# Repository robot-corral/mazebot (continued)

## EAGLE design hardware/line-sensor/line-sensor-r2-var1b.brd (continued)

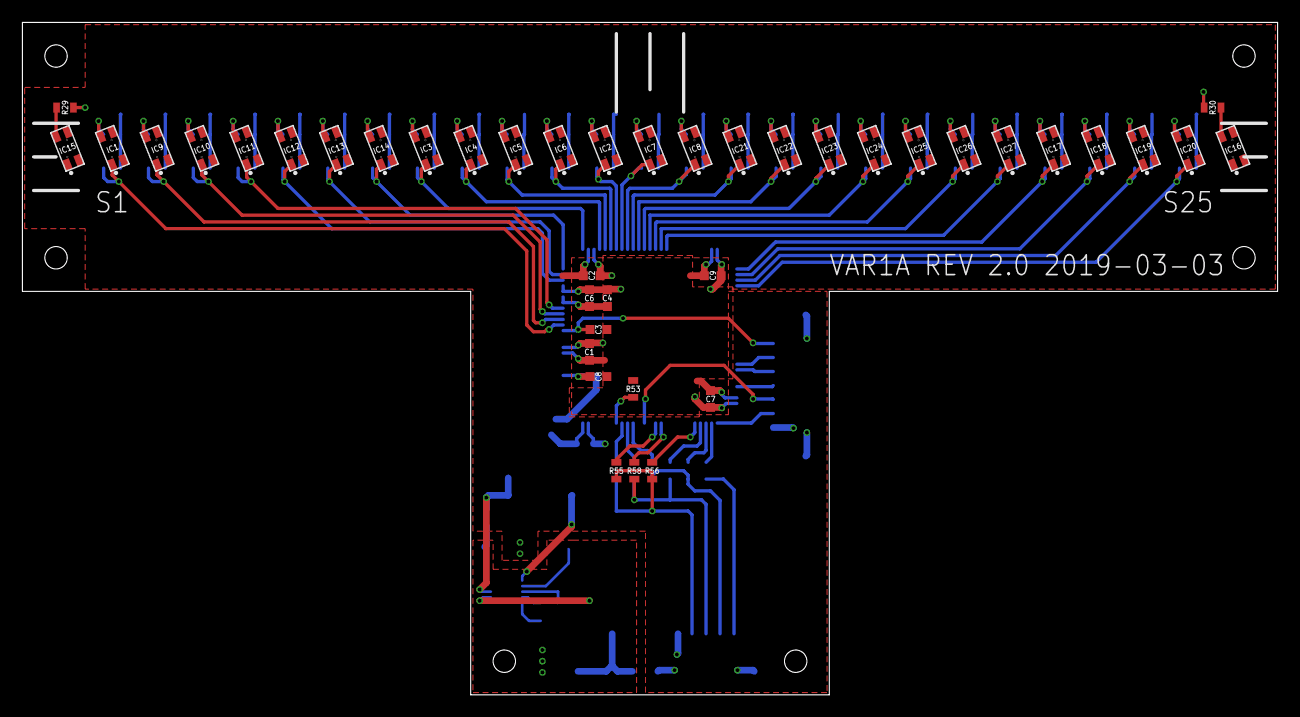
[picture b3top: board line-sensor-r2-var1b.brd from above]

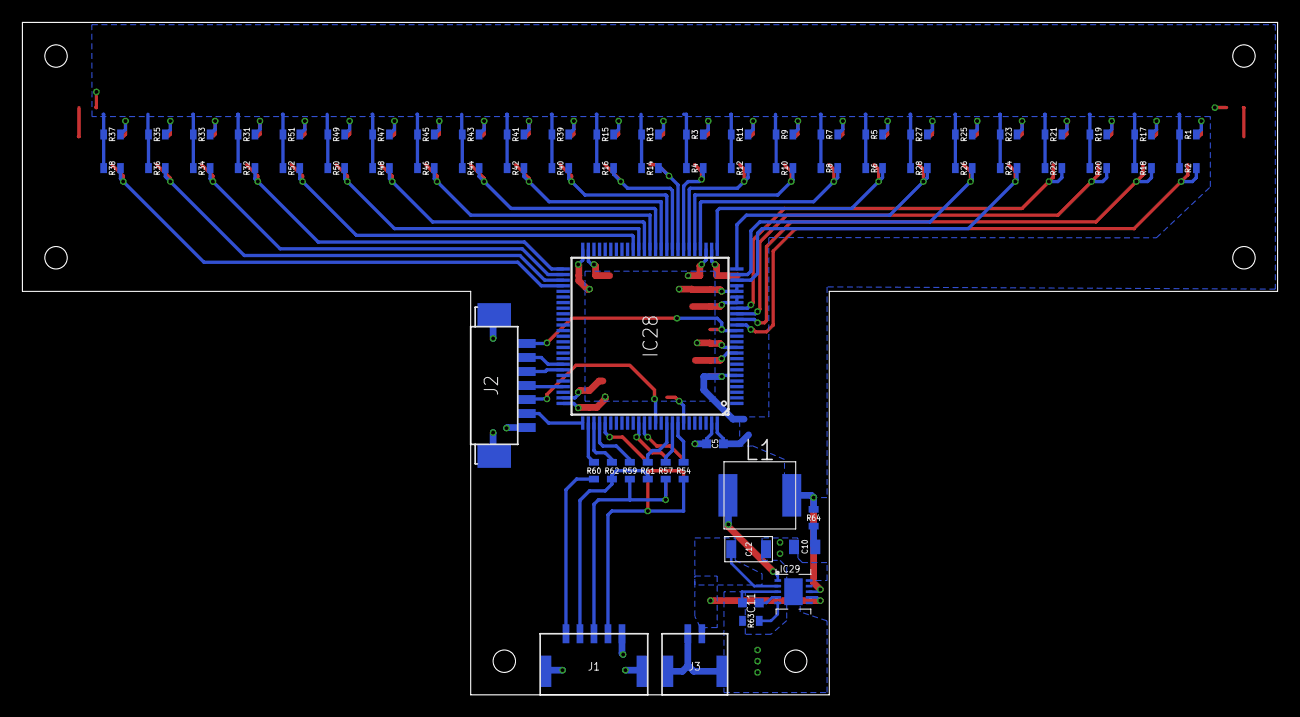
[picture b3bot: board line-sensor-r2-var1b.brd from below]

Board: 2 copper layers, 112.0 x 60.0 mm, 109 parts (68 on the bottom side), 79 nets.

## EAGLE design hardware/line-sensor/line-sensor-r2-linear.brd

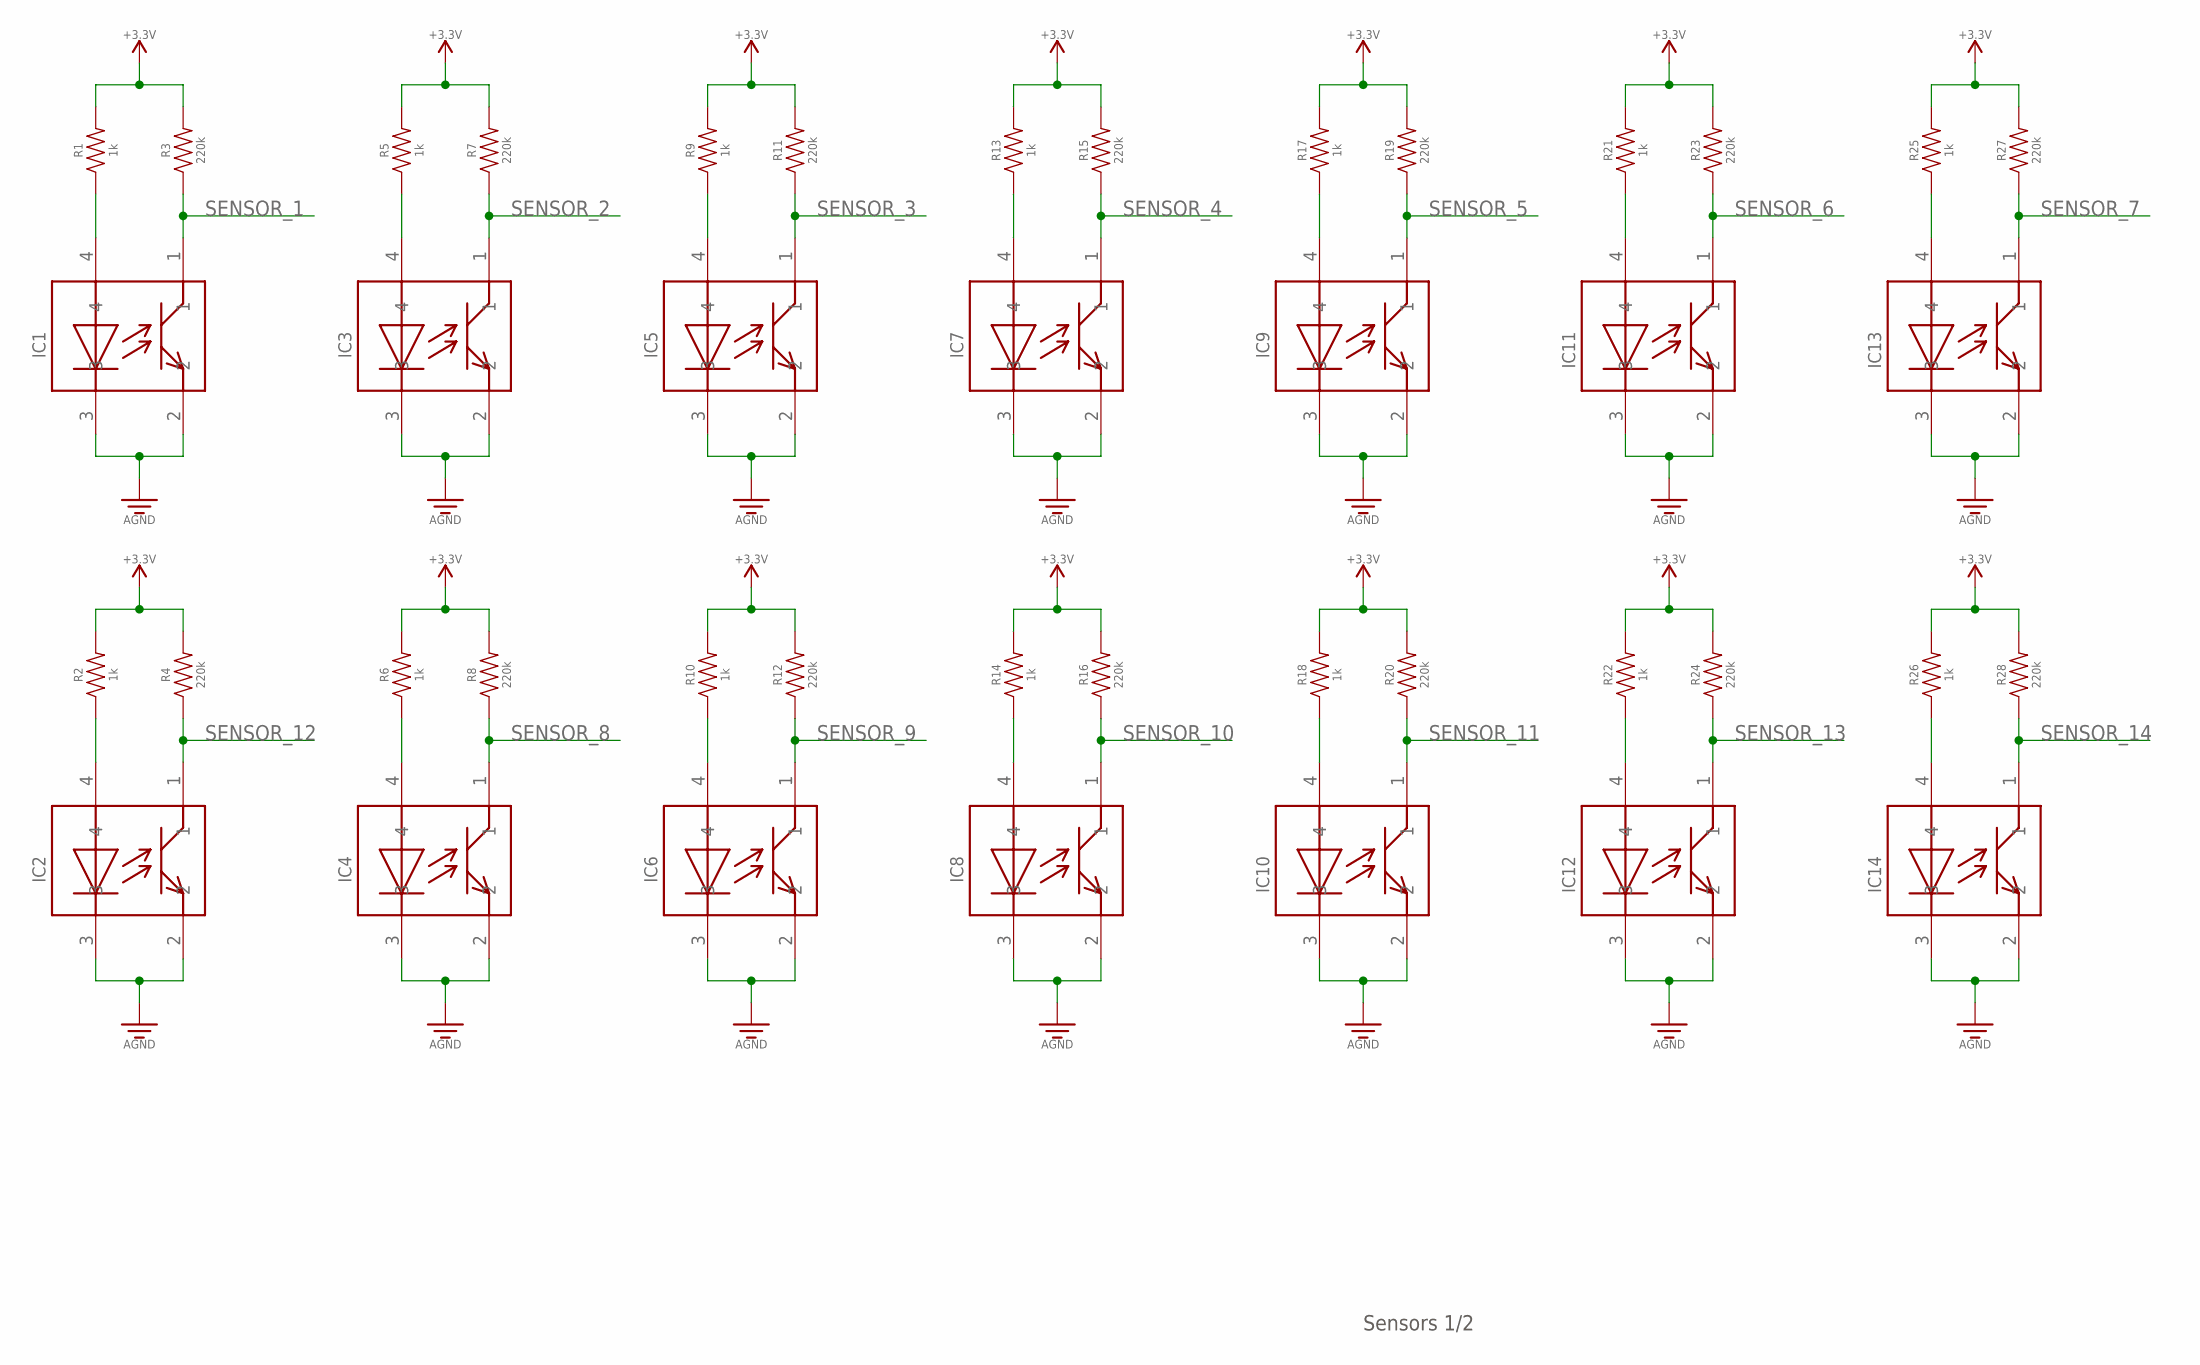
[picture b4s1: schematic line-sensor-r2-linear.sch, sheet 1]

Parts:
IC1, IC2, IC3, IC4, IC5, IC6, IC7, IC8, IC9, IC10, IC11, IC12, IC13, IC14: GP2S60
R1, R2, R5, R6, R9, R10, R13, R14, R17, R18, R21, R22, R25, R26: 1k; RESISTOR-0603
R3, R4, R7, R8, R11, R12, R15, R16, R19, R20, R23, R24, R27, R28: 220k; RESISTOR-0603

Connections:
GND: IC1.2, IC1.3, IC2.2, IC2.3, IC3.2, IC3.3, IC4.2, IC4.3, IC5.2, IC5.3, IC6.2, IC6.3, IC7.2, IC7.3, IC8.2, IC8.3, IC9.2, IC9.3, IC10.2, IC10.3, IC11.2, IC11.3, IC12.2, IC12.3, IC13.2, IC13.3, IC14.2, IC14.3; also elsewhere on the board
unnamed: IC3.4, R5.P$1 (1)
unnamed: IC1.4, R1.P$1 (1)
unnamed: IC5.4, R9.P$1 (1)
unnamed: IC7.4, R13.P$1 (1)
unnamed: IC9.4, R17.P$1 (1)
unnamed: IC11.4, R21.P$1 (1)
unnamed: IC13.4, R25.P$1 (1)
unnamed: IC4.4, R6.P$1 (1)
unnamed: IC6.4, R10.P$1 (1)
unnamed: IC8.4, R14.P$1 (1)
unnamed: IC10.4, R18.P$1 (1)
unnamed: IC2.4, R2.P$1 (1)
unnamed: IC12.4, R22.P$1 (1)
unnamed: IC14.4, R26.P$1 (1)
SENSOR_1: IC1.1, R3.P$1 (1); also elsewhere on the board
SENSOR_2: IC3.1, R7.P$1 (1); also elsewhere on the board
SENSOR_3: IC5.1, R11.P$1 (1); also elsewhere on the board
SENSOR_4: IC7.1, R15.P$1 (1); also elsewhere on the board
SENSOR_5: IC9.1, R19.P$1 (1); also elsewhere on the board
SENSOR_6: IC11.1, R23.P$1 (1); also elsewhere on the board
SENSOR_7: IC13.1, R27.P$1 (1); also elsewhere on the board
SENSOR_8: IC4.1, R8.P$1 (1); also elsewhere on the board
SENSOR_9: IC6.1, R12.P$1 (1); also elsewhere on the board
SENSOR_10: IC8.1, R16.P$1 (1); also elsewhere on the board
SENSOR_11: IC10.1, R20.P$1 (1); also elsewhere on the board
SENSOR_12: IC2.1, R4.P$1 (1); also elsewhere on the board
SENSOR_13: IC12.1, R24.P$1 (1); also elsewhere on the board
SENSOR_14: IC14.1, R28.P$1 (1); also elsewhere on the board
VDDA: R1.P$2 (2), R2.P$2 (2), R3.P$2 (2), R4.P$2 (2), R5.P$2 (2), R6.P$2 (2), R7.P$2 (2), R8.P$2 (2), R9.P$2 (2), R10.P$2 (2), R11.P$2 (2), R12.P$2 (2), R13.P$2 (2), R14.P$2 (2), R15.P$2 (2), R16.P$2 (2), R17.P$2 (2), R18.P$2 (2), R19.P$2 (2), R20.P$2 (2), R21.P$2 (2), R22.P$2 (2), R23.P$2 (2), R24.P$2 (2), R25.P$2 (2), R26.P$2 (2), R27.P$2 (2), R28.P$2 (2); also elsewhere on the board

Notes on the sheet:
Sensors 1/2

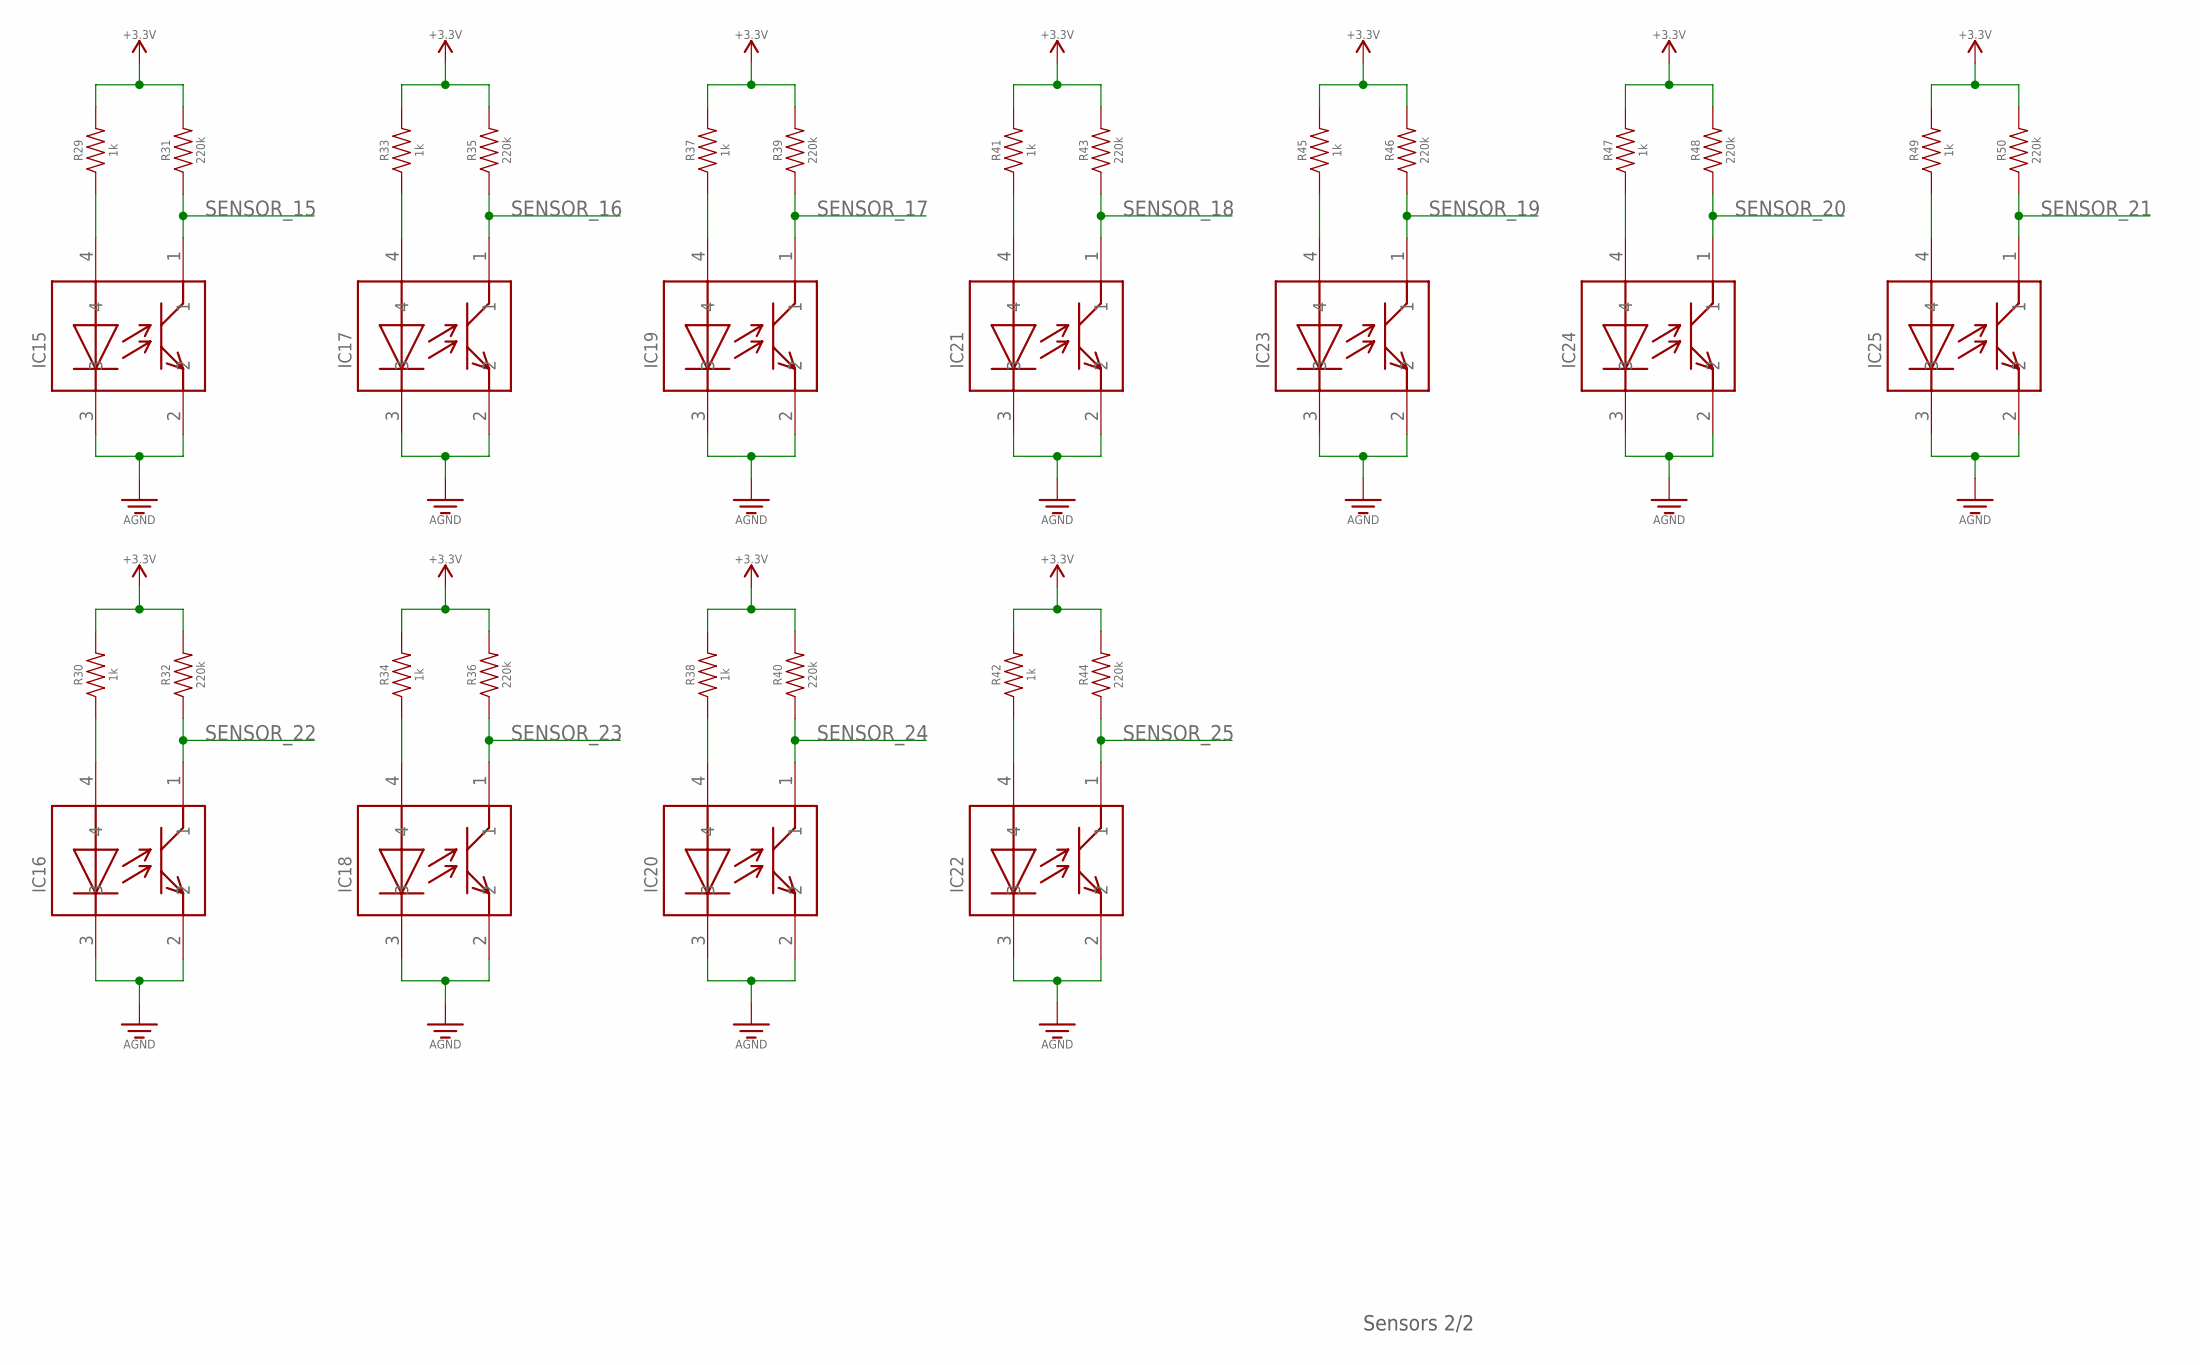
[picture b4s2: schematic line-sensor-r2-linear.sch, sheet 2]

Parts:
IC15, IC16, IC17, IC18, IC19, IC20, IC21, IC22, IC23, IC24, IC25: GP2S60
R29, R30, R33, R34, R37, R38, R41, R42, R45, R47, R49: 1k; RESISTOR-0603
R31, R32, R35, R36, R39, R40, R43, R44, R46, R48, R50: 220k; RESISTOR-0603

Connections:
GND: IC15.2, IC15.3, IC16.2, IC16.3, IC17.2, IC17.3, IC18.2, IC18.3, IC19.2, IC19.3, IC20.2, IC20.3, IC21.2, IC21.3, IC22.2, IC22.3, IC23.2, IC23.3, IC24.2, IC24.3, IC25.2, IC25.3; also elsewhere on the board
unnamed: IC15.4, R29.P$1 (1)
unnamed: IC17.4, R33.P$1 (1)
unnamed: IC19.4, R37.P$1 (1)
unnamed: IC21.4, R41.P$1 (1)
unnamed: IC23.4, R45.P$1 (1)
unnamed: IC24.4, R47.P$1 (1)
unnamed: IC25.4, R49.P$1 (1)
unnamed: IC16.4, R30.P$1 (1)
unnamed: IC18.4, R34.P$1 (1)
unnamed: IC20.4, R38.P$1 (1)
unnamed: IC22.4, R42.P$1 (1)
SENSOR_15: IC15.1, R31.P$1 (1); also elsewhere on the board
SENSOR_16: IC17.1, R35.P$1 (1); also elsewhere on the board
SENSOR_17: IC19.1, R39.P$1 (1); also elsewhere on the board
SENSOR_18: IC21.1, R43.P$1 (1); also elsewhere on the board
SENSOR_19: IC23.1, R46.P$1 (1); also elsewhere on the board
SENSOR_20: IC24.1, R48.P$1 (1); also elsewhere on the board
SENSOR_21: IC25.1, R50.P$1 (1); also elsewhere on the board
SENSOR_22: IC16.1, R32.P$1 (1); also elsewhere on the board
SENSOR_23: IC18.1, R36.P$1 (1); also elsewhere on the board
SENSOR_24: IC20.1, R40.P$1 (1); also elsewhere on the board
SENSOR_25: IC22.1, R44.P$1 (1); also elsewhere on the board
VDDA: R29.P$2 (2), R30.P$2 (2), R31.P$2 (2), R32.P$2 (2), R33.P$2 (2), R34.P$2 (2), R35.P$2 (2), R36.P$2 (2), R37.P$2 (2), R38.P$2 (2), R39.P$2 (2), R40.P$2 (2), R41.P$2 (2), R42.P$2 (2), R43.P$2 (2), R44.P$2 (2), R45.P$2 (2), R46.P$2 (2), R47.P$2 (2), R48.P$2 (2), R49.P$2 (2), R50.P$2 (2); also elsewhere on the board

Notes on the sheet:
Sensors 2/2

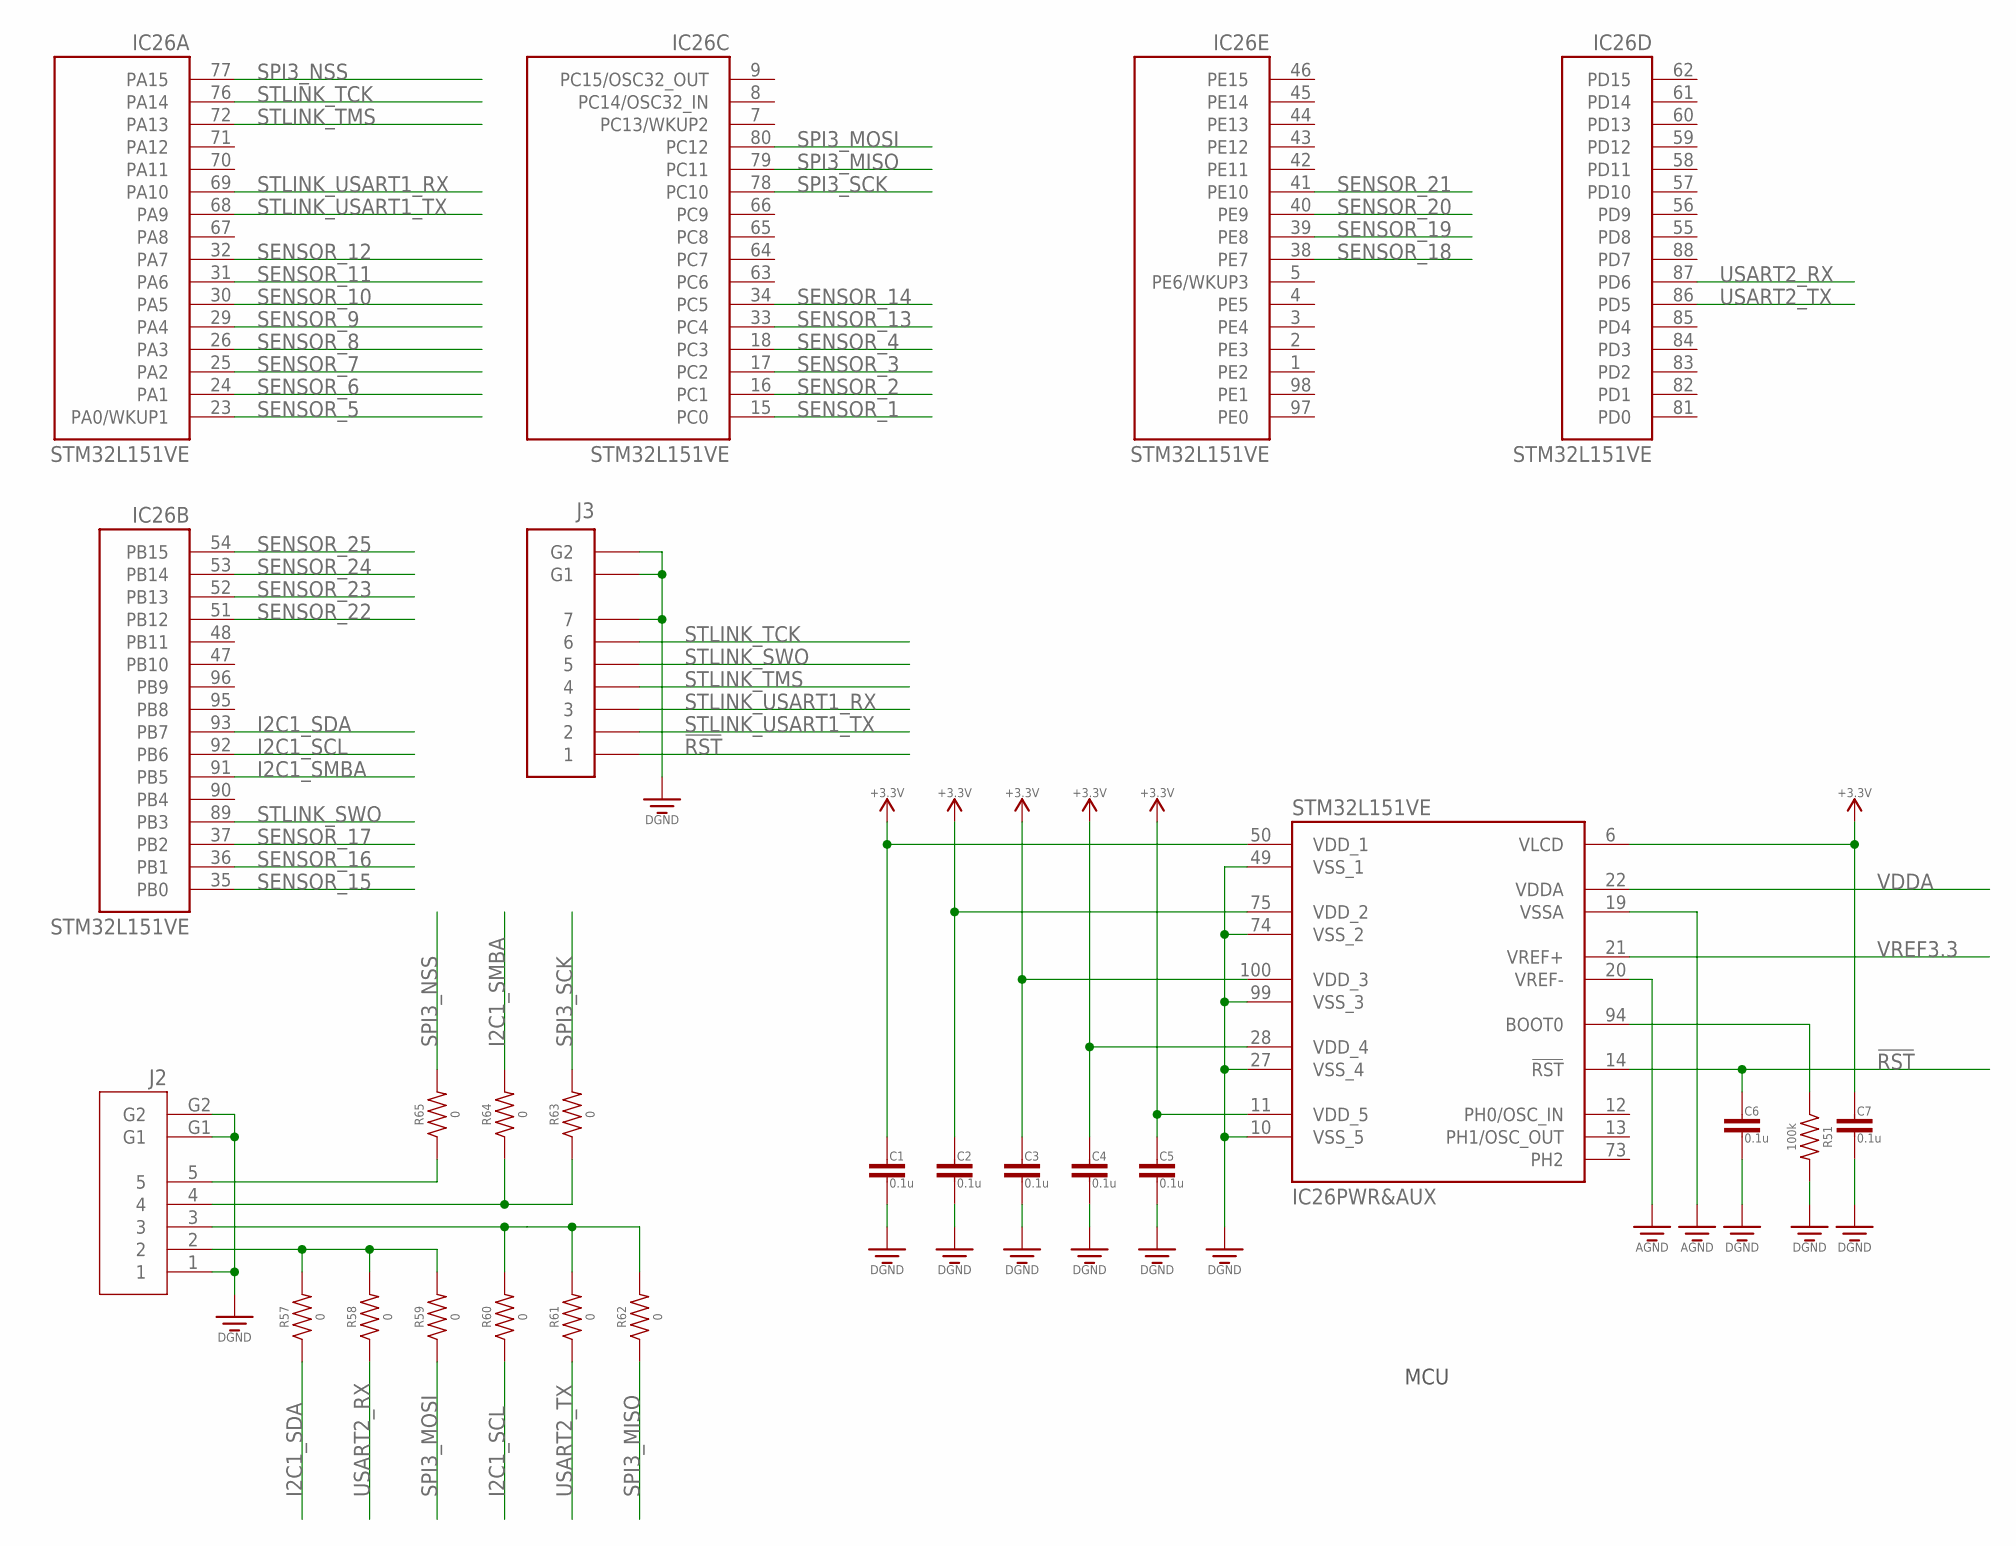
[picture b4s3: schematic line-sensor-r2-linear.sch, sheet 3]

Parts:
C1, C2, C3, C4, C5, C6, C7: 0.1u; CAPACITOR-0603
IC26: STM32L151VE; LQFP100_14X14
J2: MOLEX-502382-05XX
J3: MOLEX-53261-0771
R51: 100k; RESISTOR-0603
R57, R58, R59, R60, R61, R62, R63, R64, R65: 0; RESISTOR-0603

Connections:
!RST: C6.1, IC26.14 (!RST!), J3.1
BOOT0: IC26.94 (BOOT0), R51.P$1 (1)
GND: C1.2, C2.2, C3.2, C4.2, C5.2, C6.2, C7.2, IC26.10 (VSS_5), IC26.19 (VSSA), IC26.20 (VREF-), IC26.27 (VSS_4), IC26.49 (VSS_1), IC26.74 (VSS_2), IC26.99 (VSS_3), J2.1, J2.G1, J2.G2, J3.7, J3.G1, J3.G2, R51.P$2 (2); also elsewhere on the board
I2C1_SCL: IC26.92 (PB6), R60.P$1 (1)
I2C1_SDA: IC26.93 (PB7), R57.P$1 (1)
I2C1_SMBA: IC26.91 (PB5), R64.P$2 (2)
unnamed: J2.2, R57.P$2 (2), R58.P$2 (2), R59.P$2 (2)
unnamed: J2.3, R60.P$2 (2), R61.P$2 (2), R62.P$2 (2)
unnamed: J2.4, R63.P$1 (1), R64.P$1 (1)
unnamed: J2.5, R65.P$1 (1)
SENSOR_1: IC26.15 (PC0); also elsewhere on the board
SENSOR_2: IC26.16 (PC1); also elsewhere on the board
SENSOR_3: IC26.17 (PC2); also elsewhere on the board
SENSOR_4: IC26.18 (PC3); also elsewhere on the board
SENSOR_5: IC26.23 (PA0/WKUP1); also elsewhere on the board
SENSOR_6: IC26.24 (PA1); also elsewhere on the board
SENSOR_7: IC26.25 (PA2); also elsewhere on the board
SENSOR_8: IC26.26 (PA3); also elsewhere on the board
SENSOR_9: IC26.29 (PA4); also elsewhere on the board
SENSOR_10: IC26.30 (PA5); also elsewhere on the board
SENSOR_11: IC26.31 (PA6); also elsewhere on the board
SENSOR_12: IC26.32 (PA7); also elsewhere on the board
SENSOR_13: IC26.33 (PC4); also elsewhere on the board
SENSOR_14: IC26.34 (PC5); also elsewhere on the board
SENSOR_15: IC26.35 (PB0); also elsewhere on the board
SENSOR_16: IC26.36 (PB1); also elsewhere on the board
SENSOR_17: IC26.37 (PB2); also elsewhere on the board
SENSOR_18: IC26.38 (PE7); also elsewhere on the board
SENSOR_19: IC26.39 (PE8); also elsewhere on the board
SENSOR_20: IC26.40 (PE9); also elsewhere on the board
SENSOR_21: IC26.41 (PE10); also elsewhere on the board
SENSOR_22: IC26.51 (PB12); also elsewhere on the board
SENSOR_23: IC26.52 (PB13); also elsewhere on the board
SENSOR_24: IC26.53 (PB14); also elsewhere on the board
SENSOR_25: IC26.54 (PB15); also elsewhere on the board
SPI3_MISO: IC26.79 (PC11), R62.P$1 (1)
SPI3_MOSI: IC26.80 (PC12), R59.P$1 (1)
SPI3_NSS: IC26.77 (PA15), R65.P$2 (2)
SPI3_SCK: IC26.78 (PC10), R63.P$2 (2)
STLINK_SWO: IC26.89 (PB3), J3.5
STLINK_TCK: IC26.76 (PA14), J3.6
STLINK_TMS: IC26.72 (PA13), J3.4
STLINK_USART1_RX: IC26.69 (PA10), J3.3
STLINK_USART1_TX: IC26.68 (PA9), J3.2
USART2_RX: IC26.87 (PD6), R58.P$1 (1)
USART2_TX: IC26.86 (PD5), R61.P$1 (1)
VDD: C1.1, C2.1, C3.1, C4.1, C5.1, C7.1, IC26.6 (VLCD), IC26.11 (VDD_5), IC26.28 (VDD_4), IC26.50 (VDD_1), IC26.75 (VDD_2), IC26.100 (VDD_3); also elsewhere on the board
VDDA: IC26.22 (VDDA); also elsewhere on the board
VREF3.3: IC26.21 (VREF+); also elsewhere on the board

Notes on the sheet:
MCU

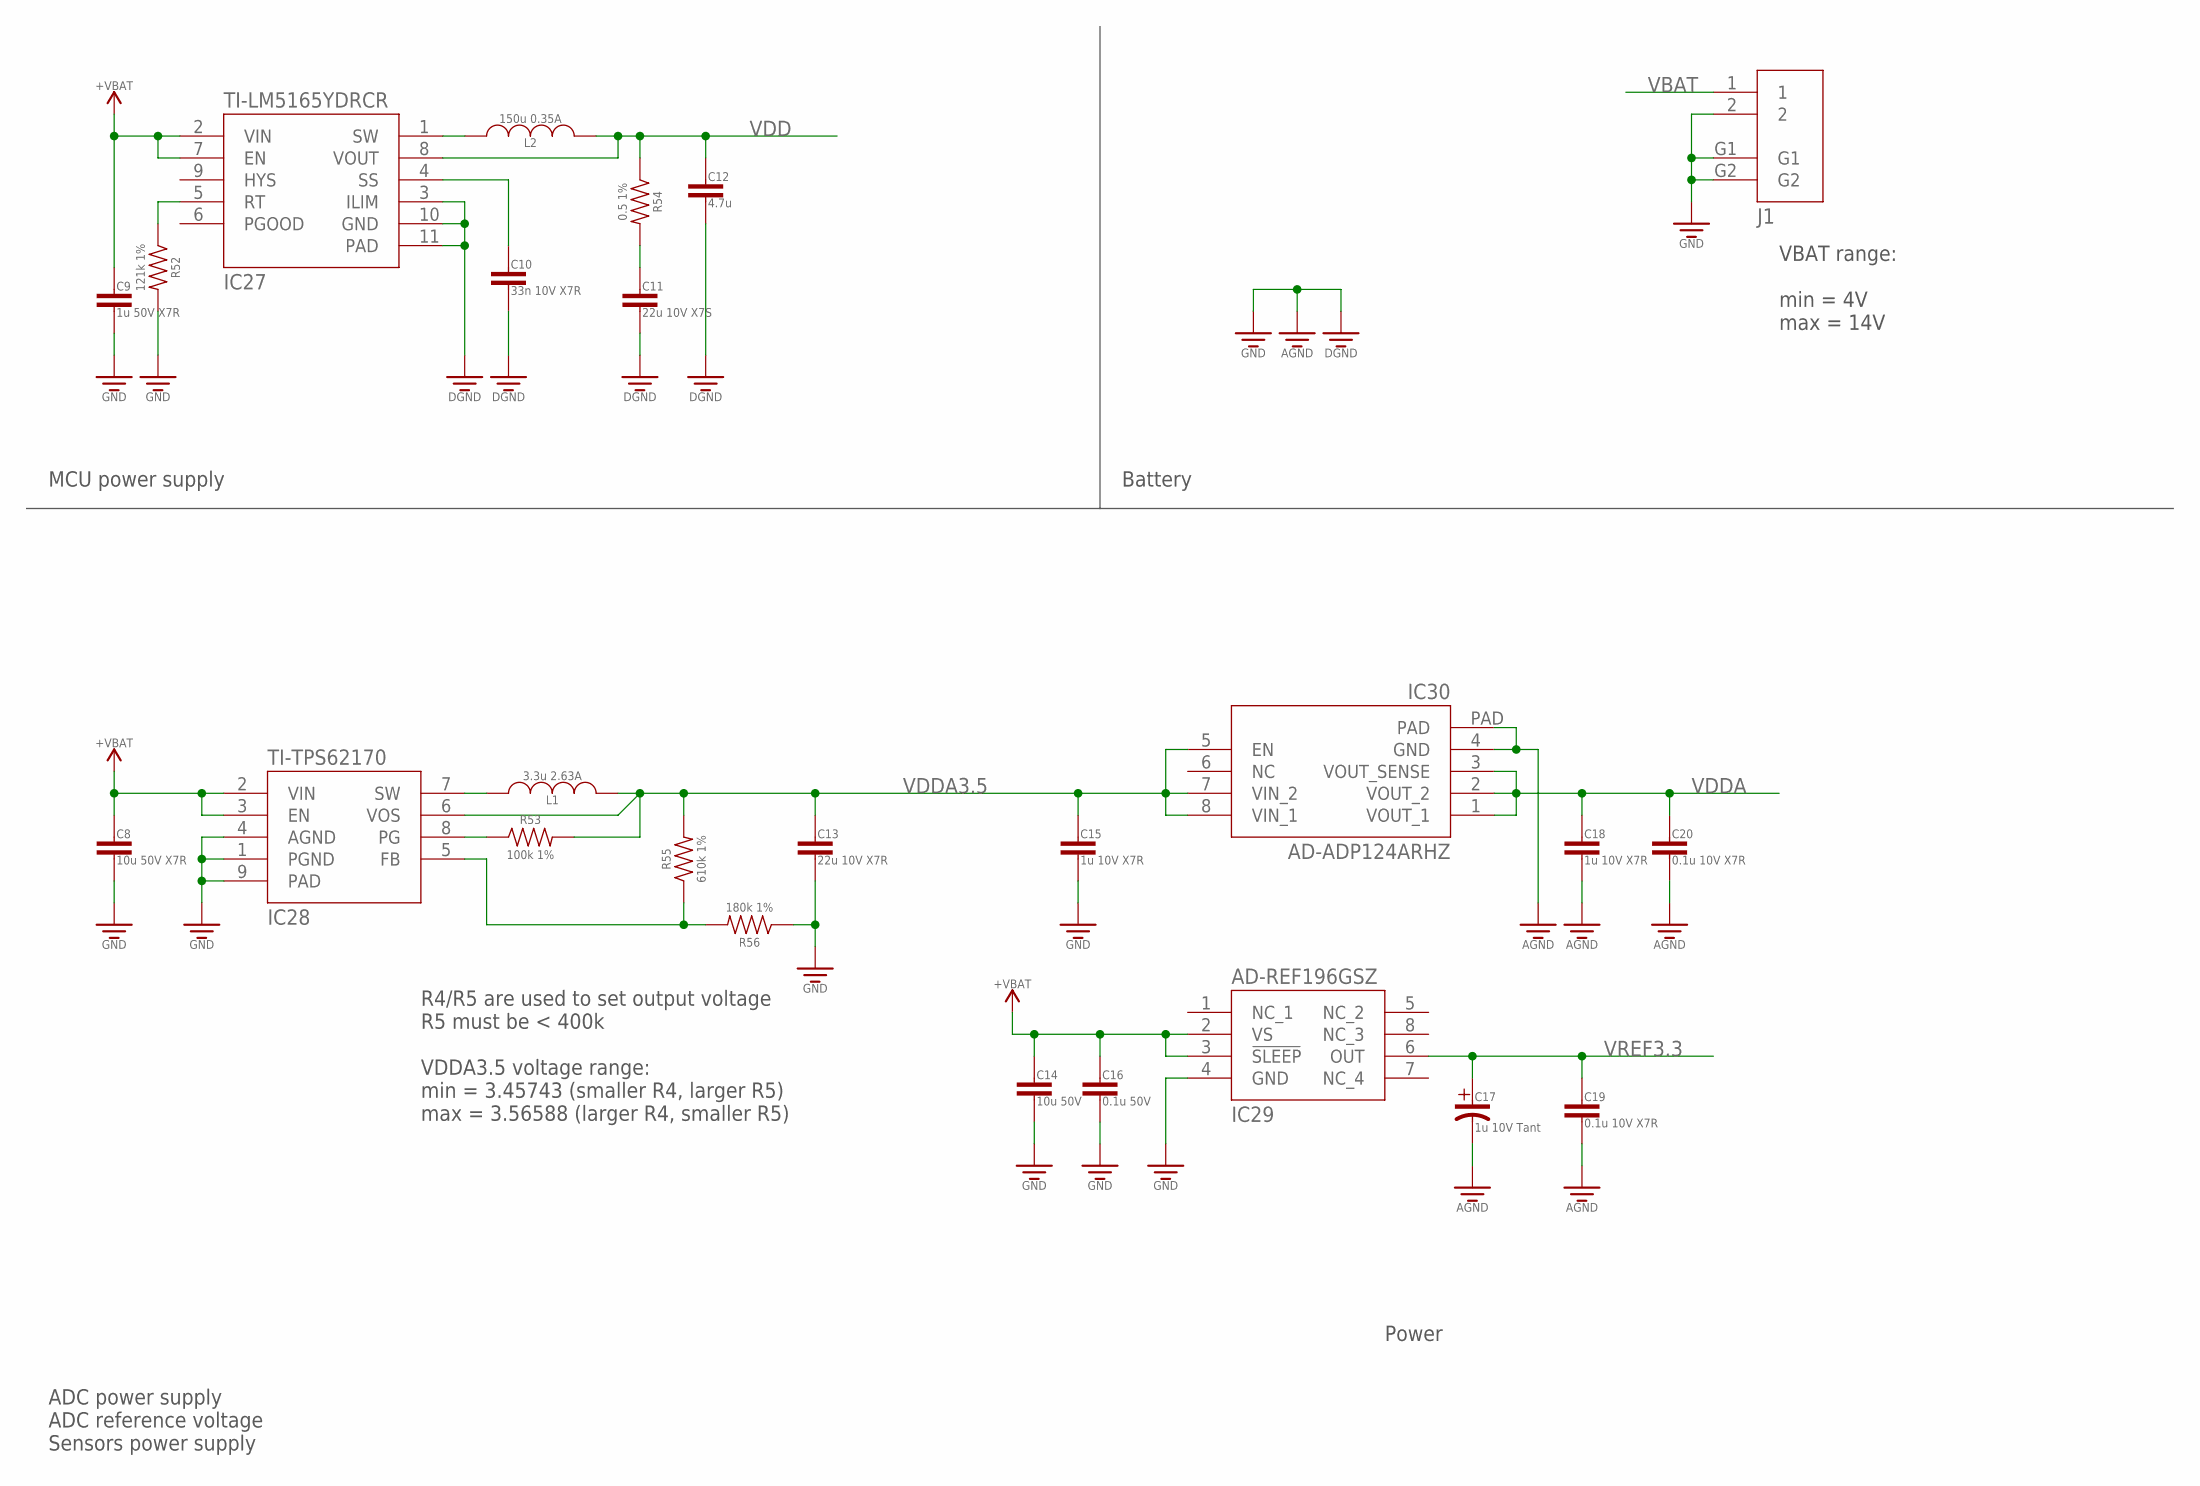
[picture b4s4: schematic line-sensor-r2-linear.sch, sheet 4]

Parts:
C8: 10u 50V X7R; CAPACITOR-0805
C9: 1u 50V X7R; CAPACITOR-1206
C10: 33n 10V X7R; CAPACITOR-0603
C11: 22u 10V X7S; CAPACITOR-0805
C12: 4.7u; CAPACITOR-0805
C13: 22u 10V X7R; CAPACITOR-0805
C14: 10u 50V; CAPACITOR-0603
C15, C18: 1u 10V X7R; CAPACITOR-0805
C16: 0.1u 50V; CAPACITOR-0603
C17: 1u 10V Tant; CAPACITOR_POLARIZED-1411-(3528-MET)
C19, C20: 0.1u 10V X7R; CAPACITOR-0603
IC27: TI-LM5165YDRCR; VSON-10-0.5MM
IC28: TI-TPS62170; WSON-8-0.5MM
IC29: AD-REF196GSZ; SOIC-8
IC30: AD-ADP124ARHZ; MSOP-8-EP
J1: MOLEX-502382-02XX
L1: 3.3u 2.63A; VLS3012HBX
L2: 150u 0.35A; ELL-6SH151M
R52: 121k 1%; RESISTOR-0603
R53: 100k 1%; RESISTOR-0603
R54: 0.5 1%; RESISTOR-0603
R55: 610k 1%; RESISTOR-0603
R56: 180k 1%; RESISTOR-0603

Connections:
GND: C8.2, C9.P$2 (2), C10.2, C11.2, C12.2, C13.2, C14.2, C15.2, C16.2, C17.NEG, C18.2, C19.2, C20.2, IC27.3 (ILIM), IC27.10 (GND), IC27.11 (PAD), IC28.1 (PGND), IC28.4 (AGND), IC28.9 (PAD), IC29.4 (GND), IC30.4 (GND), IC30.PAD, J1.2, J1.G1, J1.G2, R52.P$2 (2), R56.P$1 (1); also elsewhere on the board
IC27_SW: IC27.1 (SW), L2.1
IC28_SW: IC28.7 (SW), L1.1
unnamed: IC27.5 (RT), R52.P$1 (1)
unnamed: C10.1, IC27.4 (SS)
unnamed: C11.1, R54.P$2 (2)
unnamed: IC28.8 (PG), R53.P$1 (1)
unnamed: IC28.5 (FB), R55.P$1 (1), R56.P$2 (2)
VBAT: C8.1, C9.P$1 (1), C14.1, C16.1, IC27.2 (VIN), IC27.7 (EN), IC28.2 (VIN), IC28.3 (EN), IC29.2 (VS), IC29.3 (!SLEEP), J1.1
VDD: C12.1, IC27.8 (VOUT), L2.2, R54.P$1 (1); also elsewhere on the board
VDDA: C18.1, C20.1, IC30.1 (VOUT_1), IC30.2 (VOUT_2), IC30.3 (VOUT_SENSE); also elsewhere on the board
VDDA3.5: C13.1, C15.1, IC28.6 (VOS), IC30.5 (EN), IC30.7 (VIN_2), IC30.8 (VIN_1), L1.2, R53.P$2 (2), R55.P$2 (2)
VREF3.3: C17.POS, C19.1, IC29.6 (OUT); also elsewhere on the board

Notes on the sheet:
Power
MCU power supply
Battery
R4/R5 are used to set output voltage R5 must be < 400k VDDA3.5 voltage range: min = 3.45743 (smaller R4, larger R5) max = 3.56588 (larger R4, smaller R5)
VBAT range: min = 4V max = 14V
ADC power supply ADC reference voltage Sensors power supply

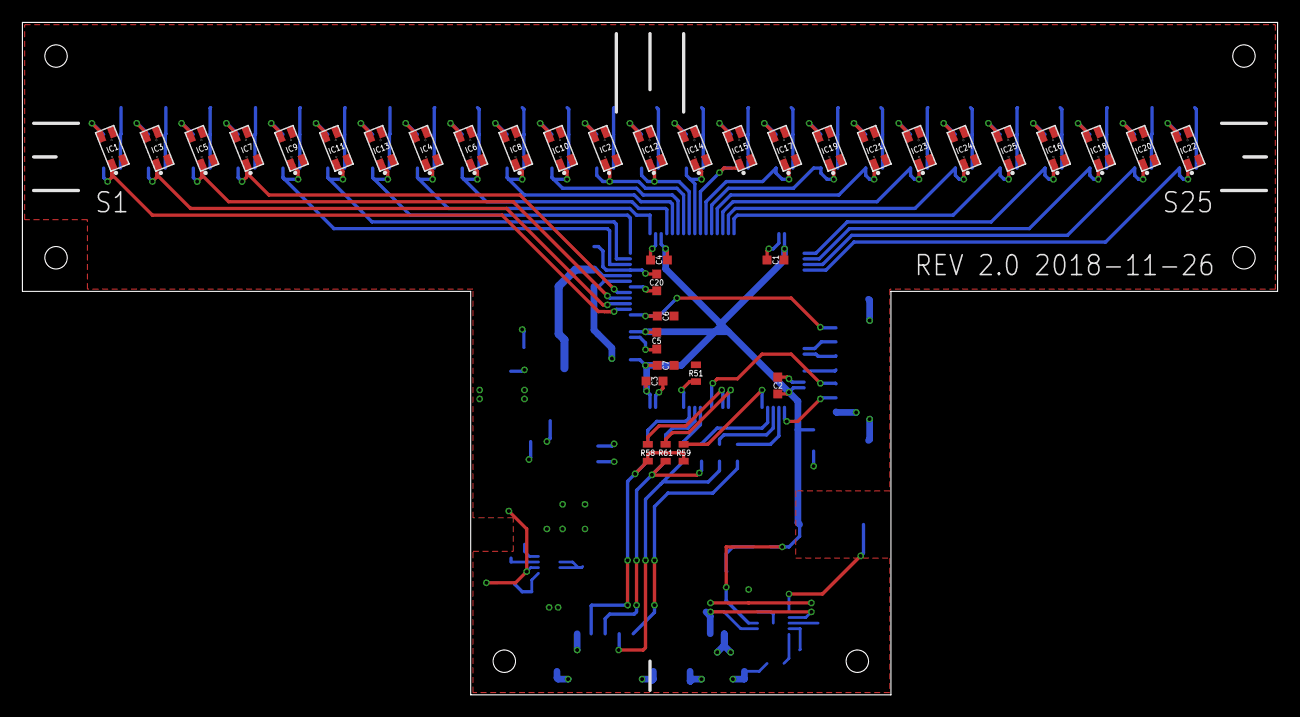
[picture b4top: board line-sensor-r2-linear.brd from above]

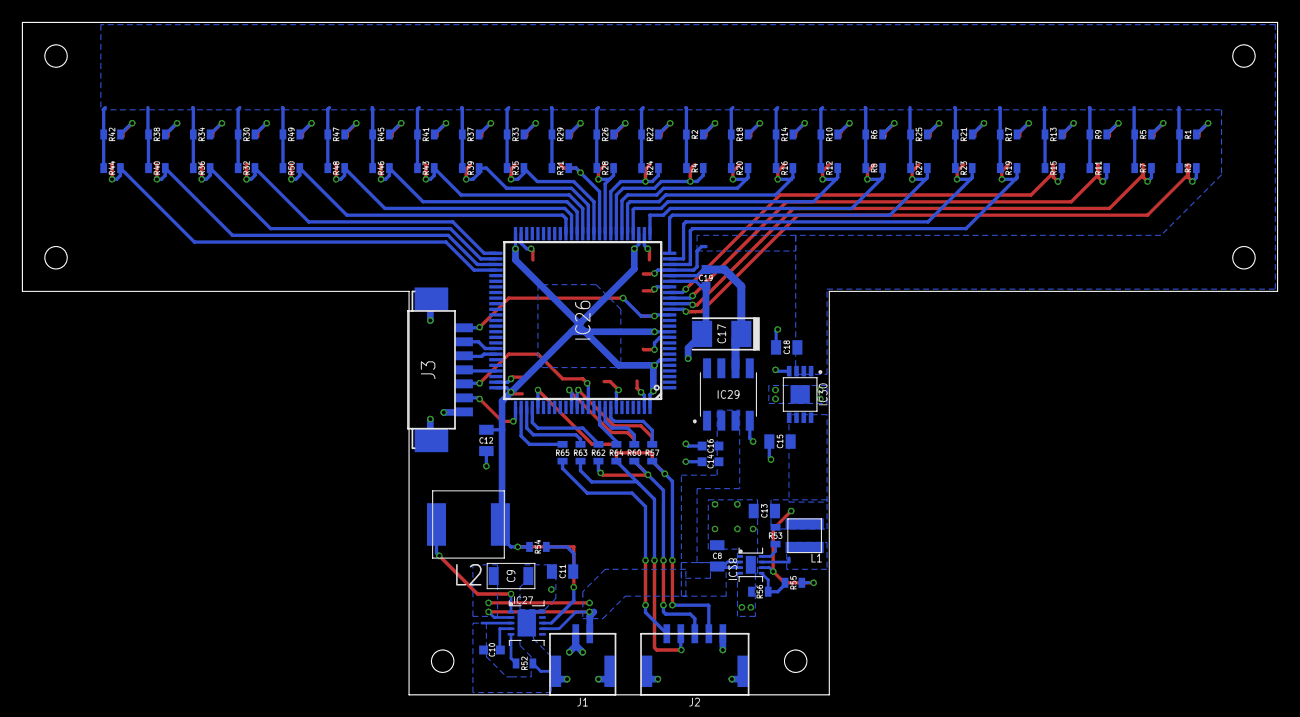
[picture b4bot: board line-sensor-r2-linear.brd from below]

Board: 2 copper layers, 112.0 x 60.0 mm, 120 parts (83 on the bottom side), 83 nets.
